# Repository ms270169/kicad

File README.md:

# kicad Projects

* [ev-charger-met16](ev-charger-met16)  
  Electrovehicle Typ 2 charger box for 7 Amps to 16 Amps  
  Details see: [ev-charger-met16/README.md](ev-charger-met16/README.md)

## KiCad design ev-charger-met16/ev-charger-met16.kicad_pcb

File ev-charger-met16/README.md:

# ev-charger-met16

## History

### V0.1: Schematic and Layout finished

----------------------------------------------
 Topic          | Description
 :----          | :-----------
 Commit         | [3cf1186470543ce20f478d2e2e48a76af5a9076f](https://github.com/ManfredSteiner/kicad/tree/3cf1186470543ce20f478d2e2e48a76af5a9076f/ev-charger-met16)
 Status         | Design finished
 Manufactured   | No
 Tested         | No
 Issue 1       | 230V Voltage transformer module [ebay 232542976388](https://www.ebay.at/itm/232542976388) not working

#### Issues

1) Voltage transformer module does not work  
   * Wrong operation amplifier on module (OP07C instead of LM358)
   * PCB error on R3 (see [netlist-reverse-engieneered.jpg](problems/voltage-tranformer_ebay-232542976388/netlist-reverse-engieneered.jpg))

   Voltage between `OUT-GND` has only a amplitude maximum of 15mV arround 0V.

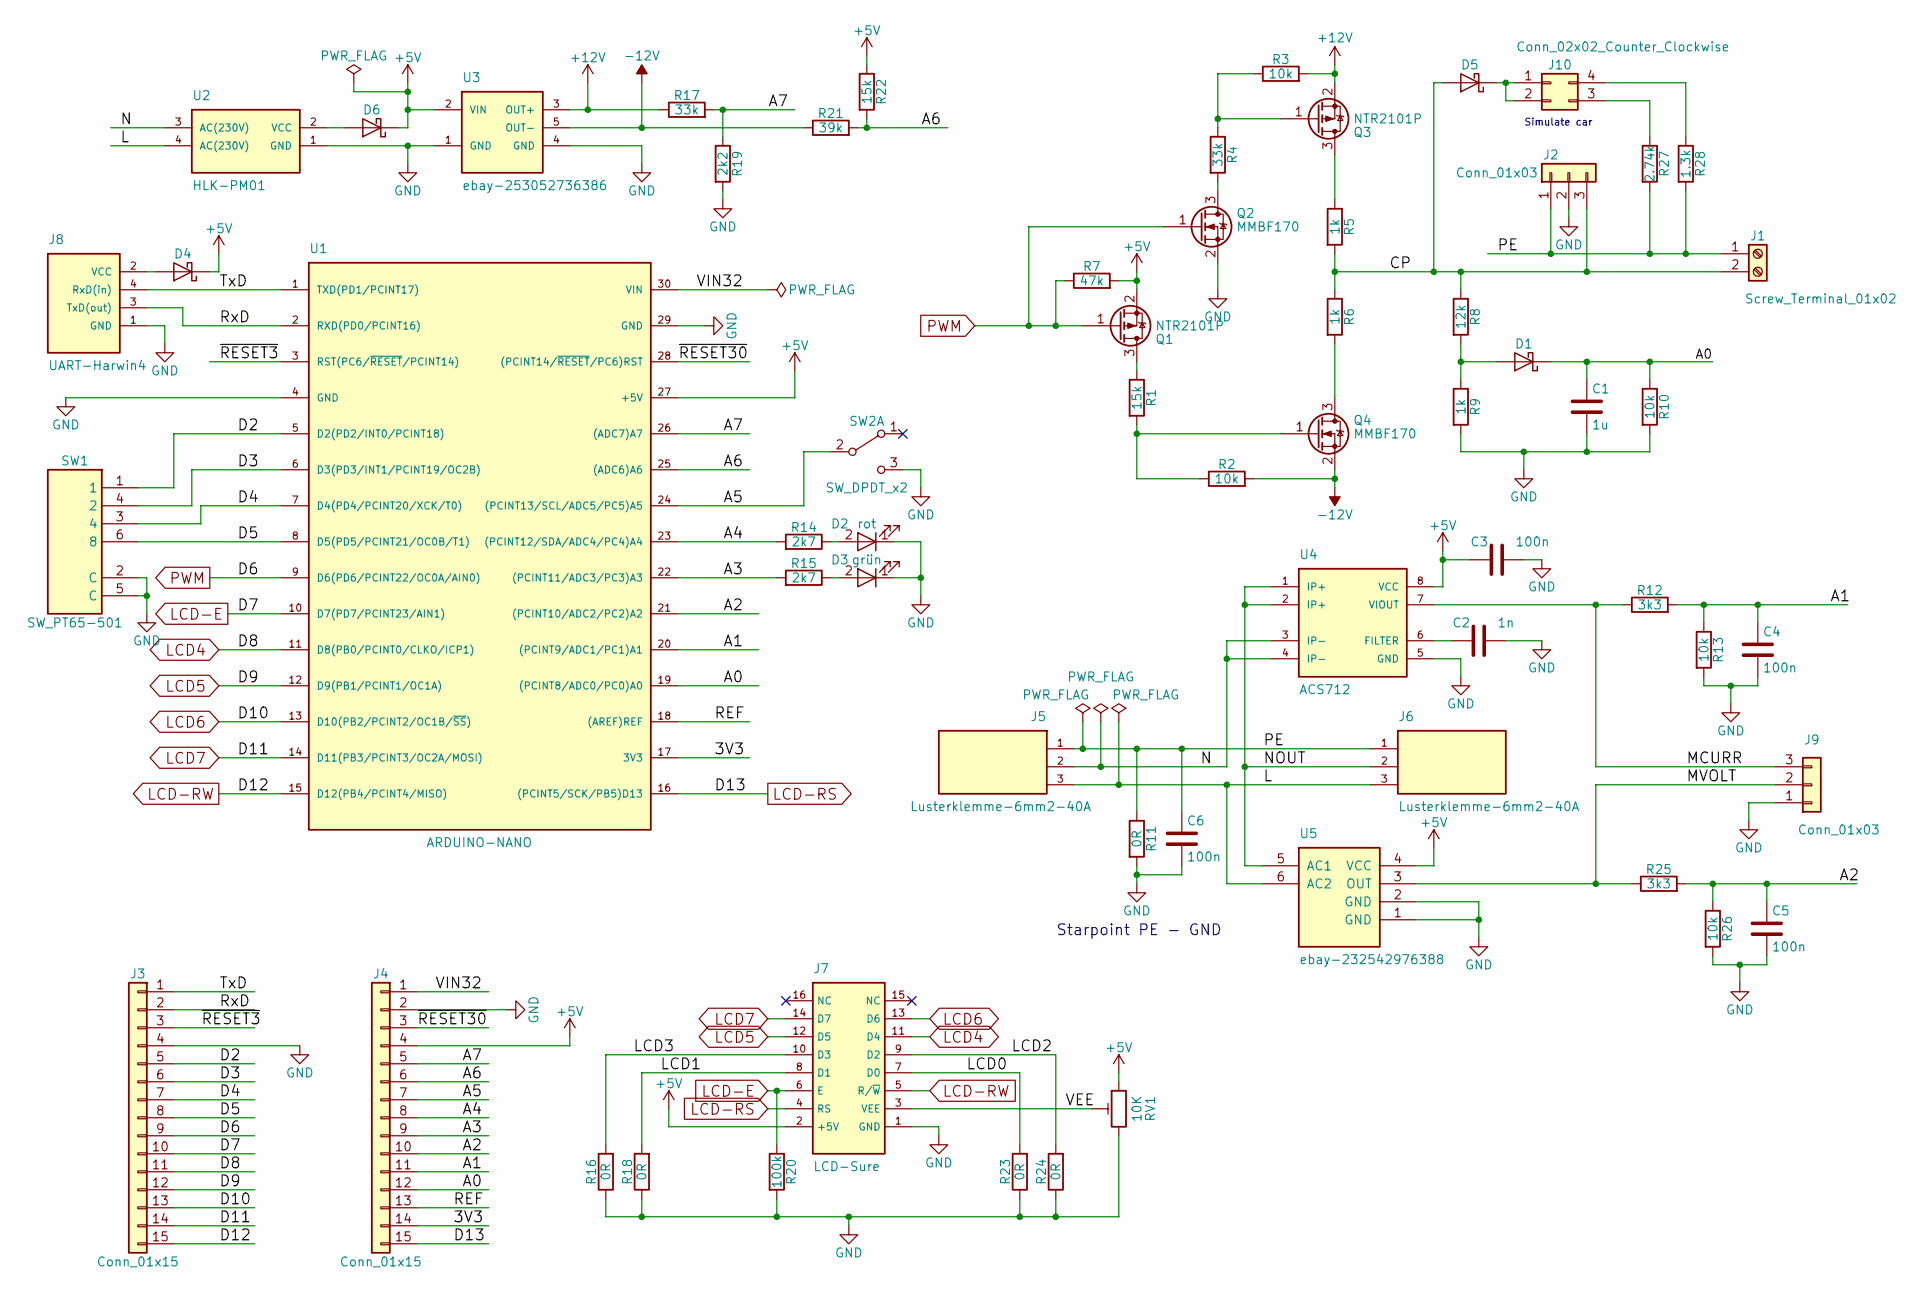
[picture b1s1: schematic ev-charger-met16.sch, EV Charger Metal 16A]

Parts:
C1: 1u; C_1210_HandSoldering
C2: 1n; C_1206_HandSoldering
C3, C4, C5, C6: 100n; C_1206_HandSoldering
D1, D4, D5: D_Schottky; D_SOD-323_HandSoldering
D2: rot; LED_PLCC-2
D3: grün; LED_PLCC-2
D6: D_Schottky; D_SMA-SMB_Universal_Handsoldering
J1: Screw_Terminal_01x02; Terminalblock-2x-5mm
J2, J9: Conn_01x03; Pin_Header_Straight_1x03_Pitch2.54mm
J3, J4: Conn_01x15; Pin_Header_Straight_1x15_Pitch2.54mm
J5: Lusterklemme-6mm2-40A; Lusterklemme-PA30P-6mm2-40A-x3-N
J6: Lusterklemme-6mm2-40A; Lusterklemme-PA30P-6mm2-40A-x3-S
J7: LCD-Sure; LCD-Sure-shifted-064
J8: UART-Harwin4; Harwin_LTek-Male_04x2.00mm_Straight_StrainRelief
J10: Conn_02x02_Counter_Clockwise; Pin_Header_Straight_2x02_Pitch2.54mm
Q1, Q3: NTR2101P; SOT-23_Handsoldering
Q2, Q4: MMBF170; SOT-23_Handsoldering
R1, R22: 15k; R_1206_HandSoldering
R2, R3, R10, R13, R26: 10k; R_1206_HandSoldering
R4, R17: 33k; R_1206_HandSoldering
R5, R6, R9: 1k; R_1206_HandSoldering
R7: 47k; R_1206_HandSoldering
R8: 12k; R_1206_HandSoldering
R11, R16, R18, R23, R24: 0R; R_1206_HandSoldering
R12, R25: 3k3; R_1206_HandSoldering
R14, R15: 2k7; R_1206_HandSoldering
R19: 2k2; R_1206_HandSoldering
R20: 100k; R_1206_HandSoldering
R21: 39k; R_1206_HandSoldering
R27: 2.74k; R_1206_HandSoldering
R28: 1.3k; R_1206_HandSoldering
RV1: 10K; Potentiometer_Trimmer_Bourns_3299W
SW1: SW_PT65-501; SW_DIP_x3_W7.62mm_PT65-501
SW2: SW_DPDT_x2; SW-ebay-171865305033
U1: ARDUINO-NANO; Arduino-Nano
U2: HLK-PM01; HLK_PM01
U3: ebay-253052736386
U4: ACS712; SO-8_5.3x6.2mm_Pitch1.27mm
U5: ebay-232542976388

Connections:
+5V: C3.2, D4.1 (K), D6.1 (K), J4.4, J7.2 (+5V), Q1.2 (S), R7.2, R22.1, RV1.1, U1.27 (+5V), U3.2 (VIN), U4.8 (VCC), U5.4 (VCC)
+12V: Q3.2 (S), R3.2, R17.1, U3.3 (OUT+)
-12V: Q4.2 (S), R2.2, R21.1, U3.5 (OUT-)
/3V3: J4.14, U1.17 (3V3)
/A0: C1.1, D1.1 (K), J4.12, R10.1, U1.19 ((PCINT8/ADC0/PC0)A0)
/A1: C4.1, J4.11, R12.2, R13.1, U1.20 ((PCINT9/ADC1/PC1)A1)
/A2: C5.1, J4.10, R25.2, R26.1, U1.21 ((PCINT10/ADC2/PC2)A2)
/A3: J4.9, R15.2, U1.22 ((PCINT11/ADC3/PC3)A3)
/A4: J4.8, R14.2, U1.23 ((PCINT12/SDA/ADC4/PC4)A4)
/A5: J4.7, SW2.2 (B), U1.24 ((PCINT13/SCL/ADC5/PC5)A5)
/A6: J4.6, R21.2, R22.2, U1.25 ((ADC6)A6)
/A7: J4.5, R17.2, R19.1, U1.26 ((ADC7)A7)
/CP: D5.2 (A), J1.2, J2.3, R5.2, R6.1, R8.1
/D2: J3.5, SW1.1, U1.5 (D2(PD2/INT0/PCINT18))
/D3: J3.6, SW1.4 (2), U1.6 (D3(PD3/INT1/PCINT19/OC2B))
/D4: J3.7, SW1.3 (4), U1.7 (D4(PD4/PCINT20/XCK/T0))
/D5: J3.8, SW1.6 (8), U1.8 (D5(PD5/PCINT21/OC0B/T1))
/L: J5.3, J6.3, U2.4 (AC(230V)), U5.6 (AC2)
/LCD0: J7.7 (D0), R23.2
/LCD1: J7.8 (D1), R18.2
/LCD2: J7.9 (D2), R24.2
/LCD3: J7.10 (D3), R16.2
/MCURR: J9.3, R12.1, U4.7 (VIOUT)
/MVOLT: J9.2, R25.1, U5.3 (OUT)
/N: J5.2, U2.3 (AC(230V)), U4.3 (IP-), U4.4 (IP-)
/NOUT: J6.2, U4.1 (IP+), U4.2 (IP+), U5.5 (AC1)
/PE: C6.1, J1.1, J2.1, J5.1, J6.1, R11.1, R27.2, R28.2
/REF: J4.13, U1.18 ((AREF)REF)
/RxD: J3.2, J8.3 (TxD(out)), U1.2 (RXD(PD0/PCINT16))
/TxD: J3.1, J8.4 (RxD(in)), U1.1 (TXD(PD1/PCINT17))
/VEE: J7.3 (VEE), RV1.2
/VIN32: J4.1, U1.30 (VIN)
/~RESET3~: J3.3, U1.3 (RST(PC6/~RESET~/PCINT14))
/~RESET30~: J4.3, U1.28 ((PCINT14/~RESET~/PC6)RST)
GND: C1.2, C2.1, C3.1, C4.2, C5.2, C6.2, D2.1 (K), D3.1 (K), J2.2, J3.4, J4.2, J7.1 (GND), J8.1 (GND), J9.1, Q2.2 (S), R9.2, R10.2, R11.2, R13.2, R16.1, R18.1, R19.2, R20.2, R23.1, R24.1, R26.2, RV1.3, SW1.2 (C), SW1.5 (C), SW2.3 (C), U1.4 (GND), U1.29 (GND), U2.1 (GND), U3.1 (GND), U3.4 (GND), U4.5 (GND), U5.1 (GND), U5.2 (GND)
LCD4: J3.11, J7.11 (D4), U1.11 (D8(PB0/PCINT0/CLKO/ICP1))
LCD5: J3.12, J7.12 (D5), U1.12 (D9(PB1/PCINT1/OC1A))
LCD6: J3.13, J7.13 (D6), U1.13 (D10(PB2/PCINT2/OC1B/~SS~))
LCD7: J3.14, J7.14 (D7), U1.14 (D11(PB3/PCINT3/OC2A/MOSI))
LCD-E: J3.10, J7.6 (E), R20.1, U1.10 (D7(PD7/PCINT23/AIN1))
LCD-RS: J4.15, J7.4 (RS), U1.16 ((PCINT5/SCK/PB5)D13)
LCD-RW: J3.15, J7.5 (R/~W~), U1.15 (D12(PB4/PCINT4/MISO))
unnamed: C2.2, U4.6 (FILTER)
unnamed: D1.2 (A), R8.2, R9.1
unnamed: D2.2 (A), R14.1
unnamed: D3.2 (A), R15.1
unnamed: D4.2 (A), J8.2 (VCC)
unnamed: D5.1 (K), J10.1, J10.2
unnamed: D6.2 (A), U2.2 (VCC)
unnamed: J10.3, R27.1
unnamed: J10.4, R28.1
unnamed: Q1.3 (D), R1.1
unnamed: Q2.3 (D), R4.2
unnamed: Q3.1 (G), R3.1, R4.1
unnamed: Q3.3 (D), R5.1
unnamed: Q4.1 (G), R1.2, R2.1
unnamed: Q4.3 (D), R6.2
PWM: J3.9, Q1.1 (G), Q2.1 (G), R7.1, U1.9 (D6(PD6/PCINT22/OC0A/AIN0))

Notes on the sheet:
Starpoint PE - GND
Simulate car

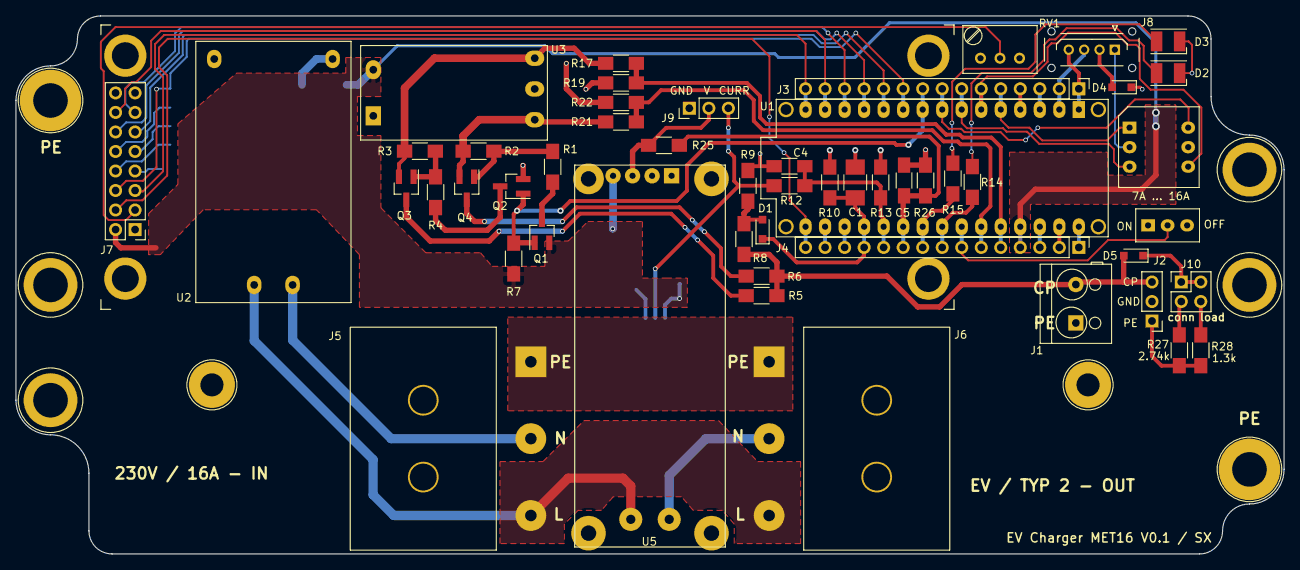
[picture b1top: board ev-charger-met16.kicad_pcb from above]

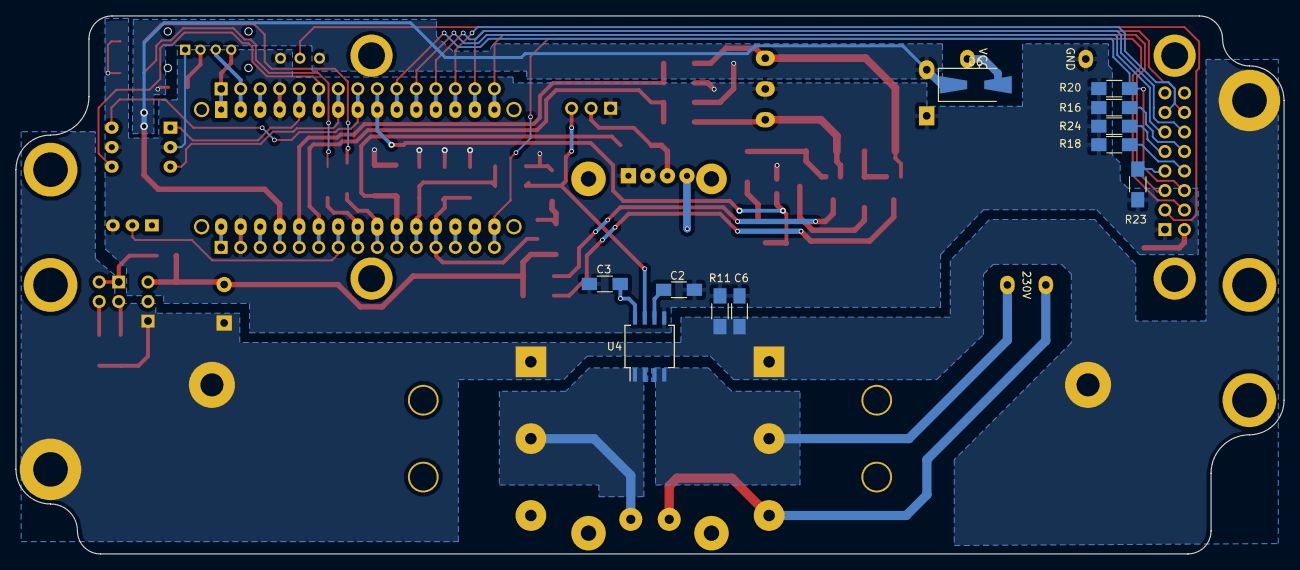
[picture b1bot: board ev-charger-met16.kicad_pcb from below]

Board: 2 copper layers, 165.0 x 70.0 mm, 62 parts (11 on the bottom side), 58 nets.

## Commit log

2018-04-19 ev-charger-met16 first commit
2018-05-12 Revision changed to 0.1
2018-05-12 V0.1 finished
